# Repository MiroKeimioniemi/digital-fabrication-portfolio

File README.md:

# Digital Fabrication Portfolio

[My Digital Fabrication Portfolio](https://digital-fabrication-portfolio-miro-keimioniemi-a2f2c11a6e705b8f.gitlab.io/) created for the 2024 [Digital Fabrication](https://www.aalto.fi/en/minors/digital-fabrication-minor) [Fab Academy](https://fabacademy.org/) overlay course at [Aalto Fablab](https://studios.aalto.fi/fablab/), containing extensive documentation for 6 months worth of hands-on learning in the domains of:
- [project management](https://digital-fabrication-portfolio-miro-keimioniemi-a2f2c11a6e705b8f.gitlab.io/p/project-management/)
- [web development](https://digital-fabrication-portfolio-miro-keimioniemi-a2f2c11a6e705b8f.gitlab.io/p/project-management/)
- [parametric 3D design and rendering](https://digital-fabrication-portfolio-miro-keimioniemi-a2f2c11a6e705b8f.gitlab.io/p/computer-aided-design/)
- [laser and vinyl cutting](https://digital-fabrication-portfolio-miro-keimioniemi-a2f2c11a6e705b8f.gitlab.io/p/computer-controlled-cutting/)
- [heat pressing](https://digital-fabrication-portfolio-miro-keimioniemi-a2f2c11a6e705b8f.gitlab.io/p/computer-controlled-cutting/)
- [CNC milling](https://digital-fabrication-portfolio-miro-keimioniemi-a2f2c11a6e705b8f.gitlab.io/p/computer-controlled-machining/)
- [electronics production](https://digital-fabrication-portfolio-miro-keimioniemi-a2f2c11a6e705b8f.gitlab.io/p/electronics-production/)
- [3D printing and scanning](https://digital-fabrication-portfolio-miro-keimioniemi-a2f2c11a6e705b8f.gitlab.io/p/3d-printing-scanning/)
- [embedded programming](https://digital-fabrication-portfolio-miro-keimioniemi-a2f2c11a6e705b8f.gitlab.io/p/embedded-programming/)
- [electronics design](https://digital-fabrication-portfolio-miro-keimioniemi-a2f2c11a6e705b8f.gitlab.io/p/electronics-design/)
- [input devices](https://digital-fabrication-portfolio-miro-keimioniemi-a2f2c11a6e705b8f.gitlab.io/p/input-devices/)
- [output devices](https://digital-fabrication-portfolio-miro-keimioniemi-a2f2c11a6e705b8f.gitlab.io/p/output-devices/)
- [molding and casting](https://digital-fabrication-portfolio-miro-keimioniemi-a2f2c11a6e705b8f.gitlab.io/p/molding-casting/)
- [networking and communications](https://digital-fabrication-portfolio-miro-keimioniemi-a2f2c11a6e705b8f.gitlab.io/p/networking-and-communications/)
- [interface and application programming](https://digital-fabrication-portfolio-miro-keimioniemi-a2f2c11a6e705b8f.gitlab.io/p/interface-and-application-programming/)
- [3-axis milling](https://digital-fabrication-portfolio-miro-keimioniemi-a2f2c11a6e705b8f.gitlab.io/p/3-axis-milling-vacuum-forming-wildcard/)
- [vacuum forming](https://digital-fabrication-portfolio-miro-keimioniemi-a2f2c11a6e705b8f.gitlab.io/p/3-axis-milling-vacuum-forming-wildcard/)
- [system integration](https://digital-fabrication-portfolio-miro-keimioniemi-a2f2c11a6e705b8f.gitlab.io/p/system-integration/) 

...creating varied unique projects such as: 
- [this website](https://digital-fabrication-portfolio-miro-keimioniemi-a2f2c11a6e705b8f.gitlab.io/p/project-management/)
- [3D renders](https://digital-fabrication-portfolio-miro-keimioniemi-a2f2c11a6e705b8f.gitlab.io/p/computer-aided-design/)
- [a parametric dragon construction kit](https://digital-fabrication-portfolio-miro-keimioniemi-a2f2c11a6e705b8f.gitlab.io/p/computer-controlled-cutting/)
- [prints on a hoodie](https://digital-fabrication-portfolio-miro-keimioniemi-a2f2c11a6e705b8f.gitlab.io/p/computer-controlled-cutting/)
- [printed circuit boards (PCB)](https://digital-fabrication-portfolio-miro-keimioniemi-a2f2c11a6e705b8f.gitlab.io/p/electronics-design/)
- [keychains](https://digital-fabrication-portfolio-miro-keimioniemi-a2f2c11a6e705b8f.gitlab.io/p/3d-printing-scanning/)
- [3D models of real objects](https://digital-fabrication-portfolio-miro-keimioniemi-a2f2c11a6e705b8f.gitlab.io/p/3d-printing-scanning/)
- [embedded games](https://digital-fabrication-portfolio-miro-keimioniemi-a2f2c11a6e705b8f.gitlab.io/p/embedded-programming/)
- [design shelves](https://digital-fabrication-portfolio-miro-keimioniemi-a2f2c11a6e705b8f.gitlab.io/p/computer-controlled-machining/)
- [lightsabers](https://digital-fabrication-portfolio-miro-keimioniemi-a2f2c11a6e705b8f.gitlab.io/p/molding-casting/)
- [a mobile app](https://digital-fabrication-portfolio-miro-keimioniemi-a2f2c11a6e705b8f.gitlab.io/p/interface-and-application-programming/) 

...and most notably; [a gesture controlled lamp](https://digital-fabrication-portfolio-miro-keimioniemi-a2f2c11a6e705b8f.gitlab.io/final-project/) integrating most of the processes learned into one larger prototype as the course final project.

The website is deployed at [https://digital-fabrication-portfolio-miro-keimioniemi-a2f2c11a6e705b8f.gitlab.io/](https://digital-fabrication-portfolio-miro-keimioniemi-a2f2c11a6e705b8f.gitlab.io/), which can also be found at [mirokeimioniemi.com](https://mirokeimioniemi.com/).

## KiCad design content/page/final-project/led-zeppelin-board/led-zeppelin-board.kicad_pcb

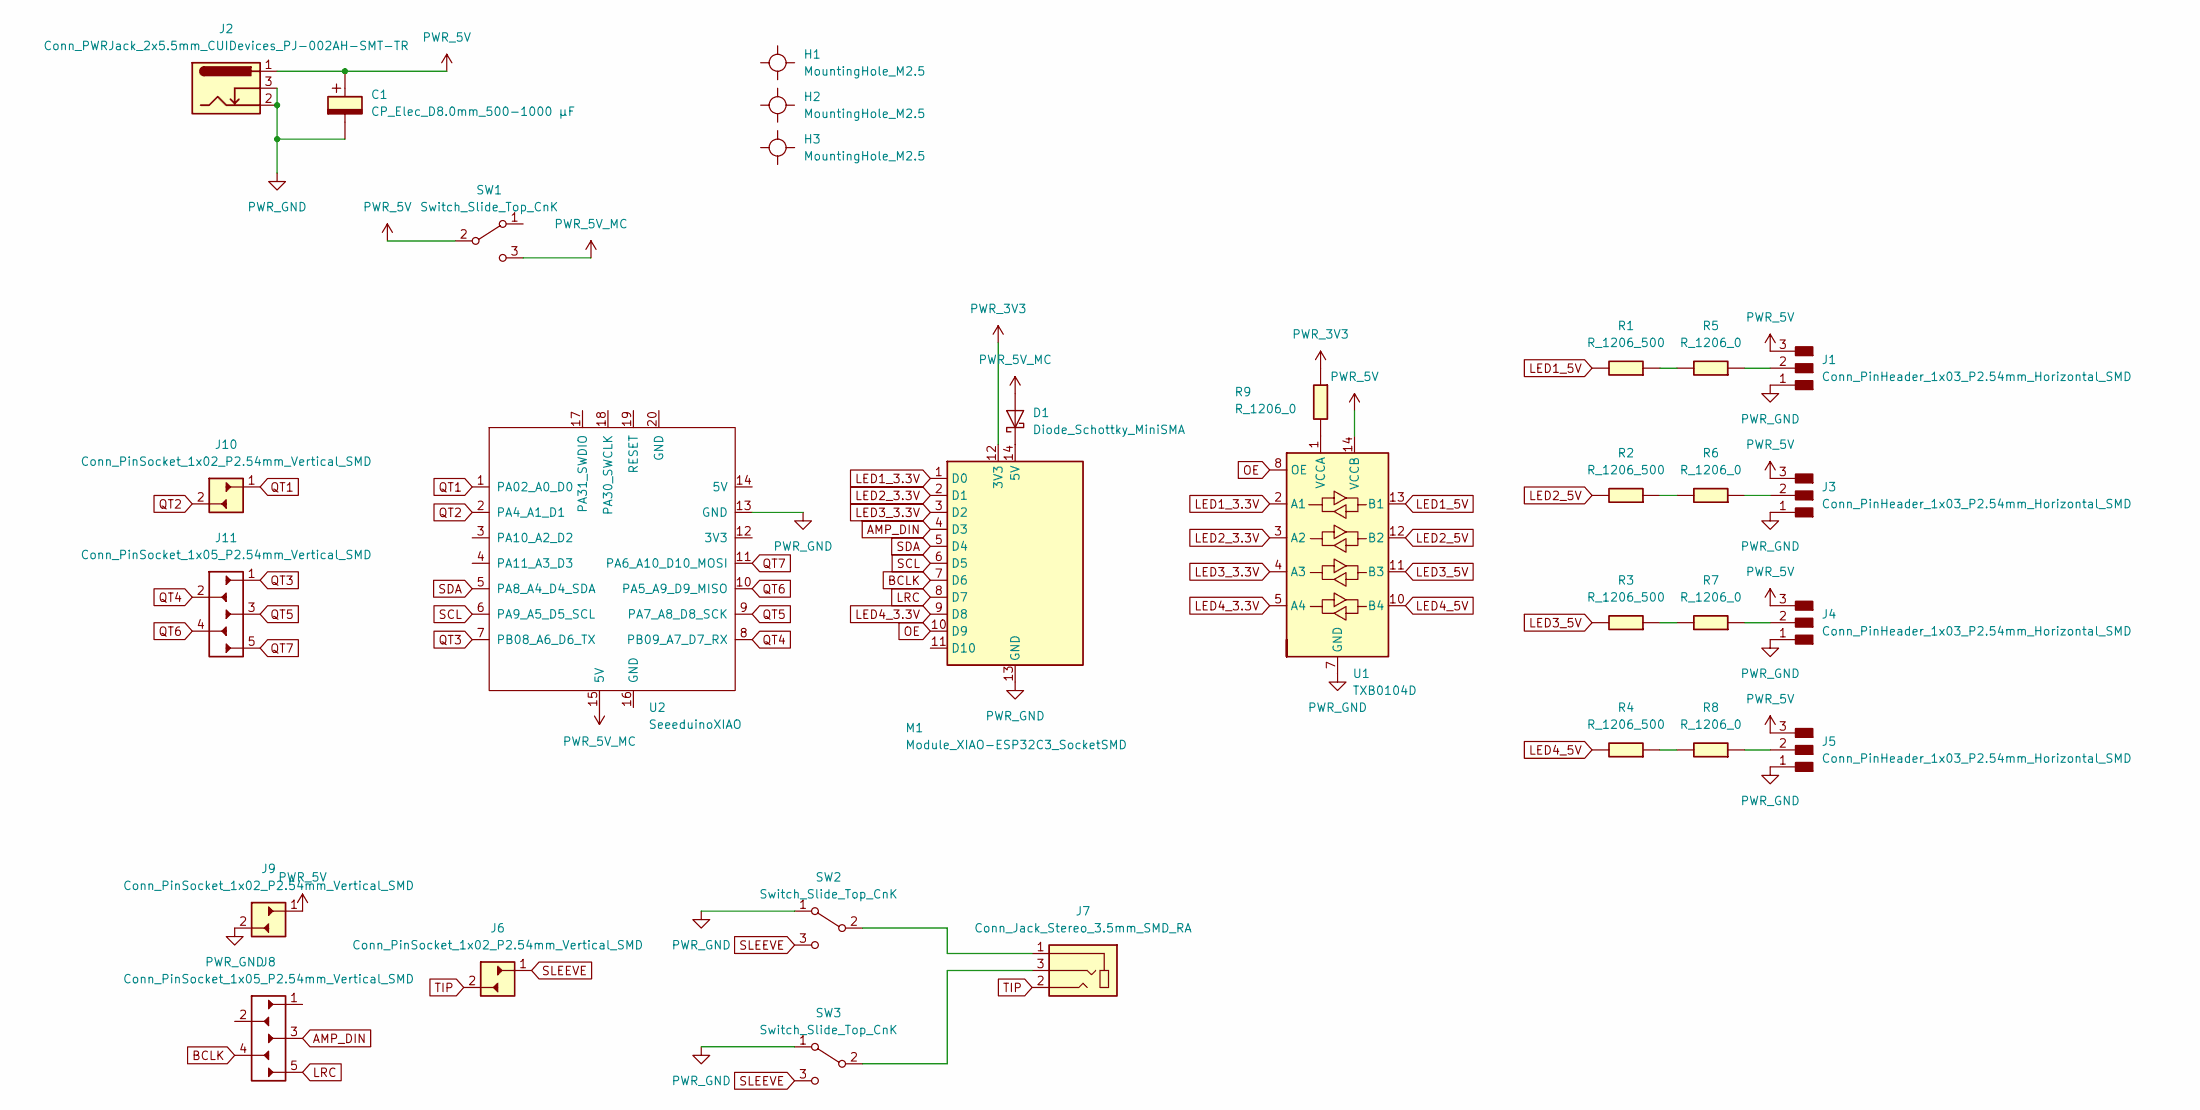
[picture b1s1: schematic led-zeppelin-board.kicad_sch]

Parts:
C1: CP_Elec_D8.0mm_500-1000 µF; CP_Elec_D8.0mm
D1: Diode_Schottky_MiniSMA; SOD-123T
H1, H2, H3: MountingHole_M2.5
J1, J3, J4, J5: Conn_PinHeader_1x03_P2.54mm_Horizontal_SMD; PinHeader_1x03_P2.54mm_Horizontal_SMD
J2: Conn_PWRJack_2x5.5mm_CUIDevices_PJ-002AH-SMT-TR; CUIDevices_PJ-002AH-SMT-TR_PWRJack_2x5.5mm
J6, J9, J10: Conn_PinSocket_1x02_P2.54mm_Vertical_SMD; PinSocket_1x02_P2.54mm_Vertical_SMD
J7: Conn_Jack_Stereo_3.5mm_SMD_RA; Conn_Jack_Stereo_3.5mm_CUI_SJ-3523-SMT-TR
J8, J11: Conn_PinSocket_1x05_P2.54mm_Vertical_SMD; PinSocket_1x05_P2.54mm_Vertical_SMD
M1: Module_XIAO-ESP32C3_SocketSMD; SeeedStudio_XIAO_SocketSMD
R1, R2, R3, R4: R_1206_500; R_1206
R5, R6, R7, R8, R9: R_1206_0; R_1206
SW1, SW2, SW3: Switch_Slide_Top_CnK; Switch_Slide_Top_CnK_JS102011JCQN_8.5x3.5mm
U1: TXB0104D; SOIC-14_3.9x8.7mm_P1.27mm
U2: SeeeduinoXIAO; SeeedStudio_XIAO_SocketSMD

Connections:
AMP_DIN: J8.3 (Pin_1), M1.4 (D3)
BCLK: J8.4 (Pin_2), M1.7 (D6)
LED1_3.3V: M1.1 (D0), U1.2 (A1)
LED1_5V: R1.1, U1.13 (B1)
LED2_3.3V: M1.2 (D1), U1.3 (A2)
LED2_5V: R2.1, U1.12 (B2)
LED3_3.3V: M1.3 (D2), U1.4 (A3)
LED3_5V: R3.1, U1.11 (B3)
LED4_3.3V: M1.9 (D8), U1.5 (A4)
LED4_5V: R4.1, U1.10 (B4)
LRC: J8.5 (Pin_1), M1.8 (D7)
unnamed: D1.1 (K), M1.14 (5V)
unnamed: J1.2, R5.2
unnamed: J3.2, R6.2
unnamed: J4.2, R7.2
unnamed: J5.2, R8.2
unnamed: R1.2, R5.1
unnamed: R2.2, R6.1
unnamed: R3.2, R7.1
unnamed: R4.2, R8.1
unnamed: J7.1, SW2.2 (B)
unnamed: J7.3, SW3.2 (B)
unnamed: R9.1, U1.1 (VCCA)
OE: M1.10 (D9), U1.8 (OE)
PWR_3V3: M1.12 (3V3), R9.2
PWR_5V: C1.1, J1.3, J2.1, J3.3, J4.3, J5.3, J9.1, SW1.2 (B), U1.14 (VCCB)
PWR_5V_MC: D1.2 (A), SW1.3 (C), U2.15 (5V)
PWR_GND: C1.2, J1.1, J2.2, J2.3, J3.1, J4.1, J5.1, J9.2, M1.13 (GND), SW2.1 (A), SW3.1 (A), U1.7 (GND), U2.13 (GND)
QT1: J10.1, U2.1 (PA02_A0_D0)
QT2: J10.2, U2.2 (PA4_A1_D1)
QT3: J11.1, U2.7 (PB08_A6_D6_TX)
QT4: J11.2, U2.8 (PB09_A7_D7_RX)
QT5: J11.3 (Pin_1), U2.9 (PA7_A8_D8_SCK)
QT6: J11.4 (Pin_2), U2.10 (PA5_A9_D9_MISO)
QT7: J11.5 (Pin_1), U2.11 (PA6_A10_D10_MOSI)
SCL: M1.6 (D5), U2.6 (PA9_A5_D5_SCL)
SDA: M1.5 (D4), U2.5 (PA8_A4_D4_SDA)
SLEEVE: J6.1, SW2.3 (C), SW3.3 (C)
TIP: J6.2, J7.2

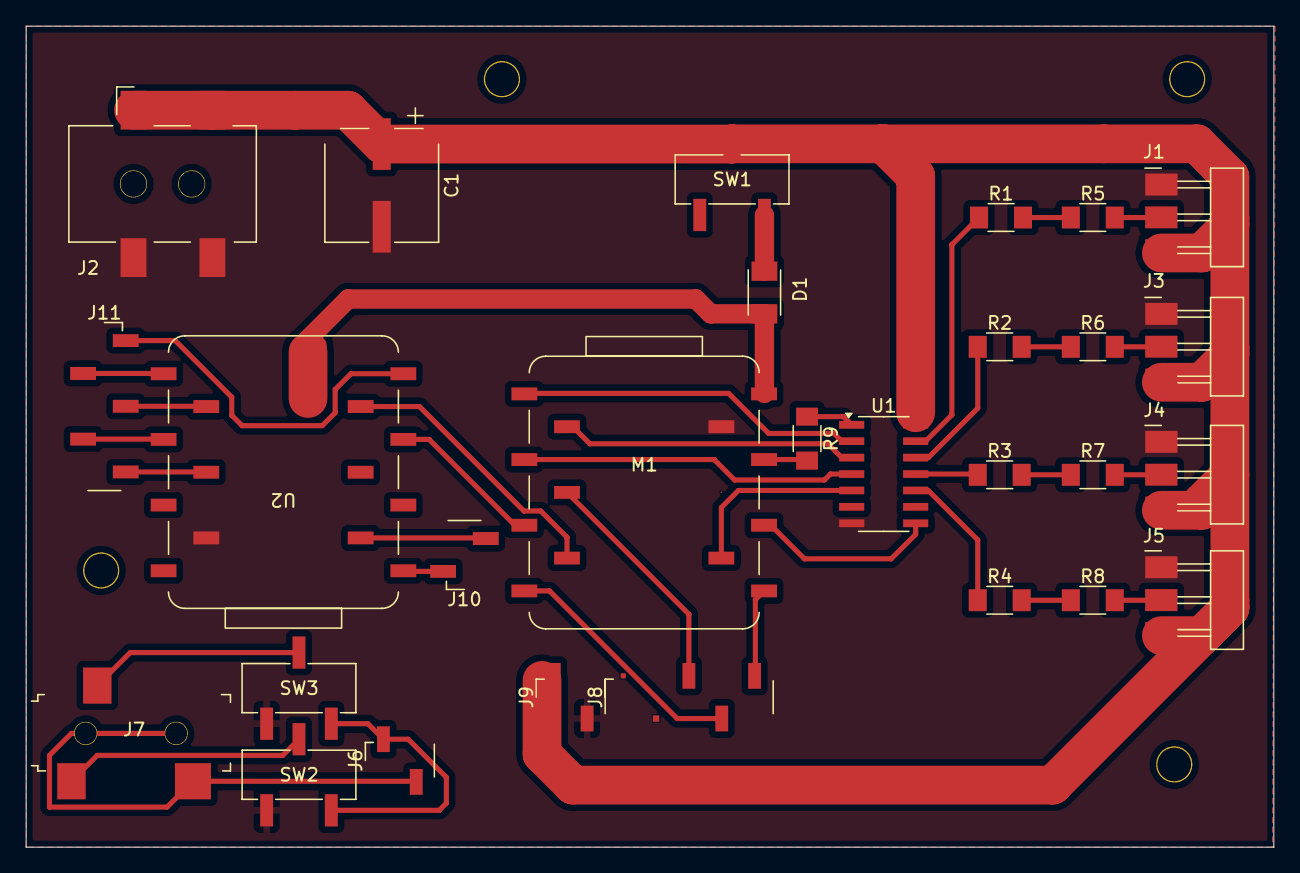
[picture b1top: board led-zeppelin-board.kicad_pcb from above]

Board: 2 copper layers, 96.5 x 63.5 mm, 32 parts (0 on the bottom side), 39 nets.

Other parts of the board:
H2#2: MountingHole_M2.5

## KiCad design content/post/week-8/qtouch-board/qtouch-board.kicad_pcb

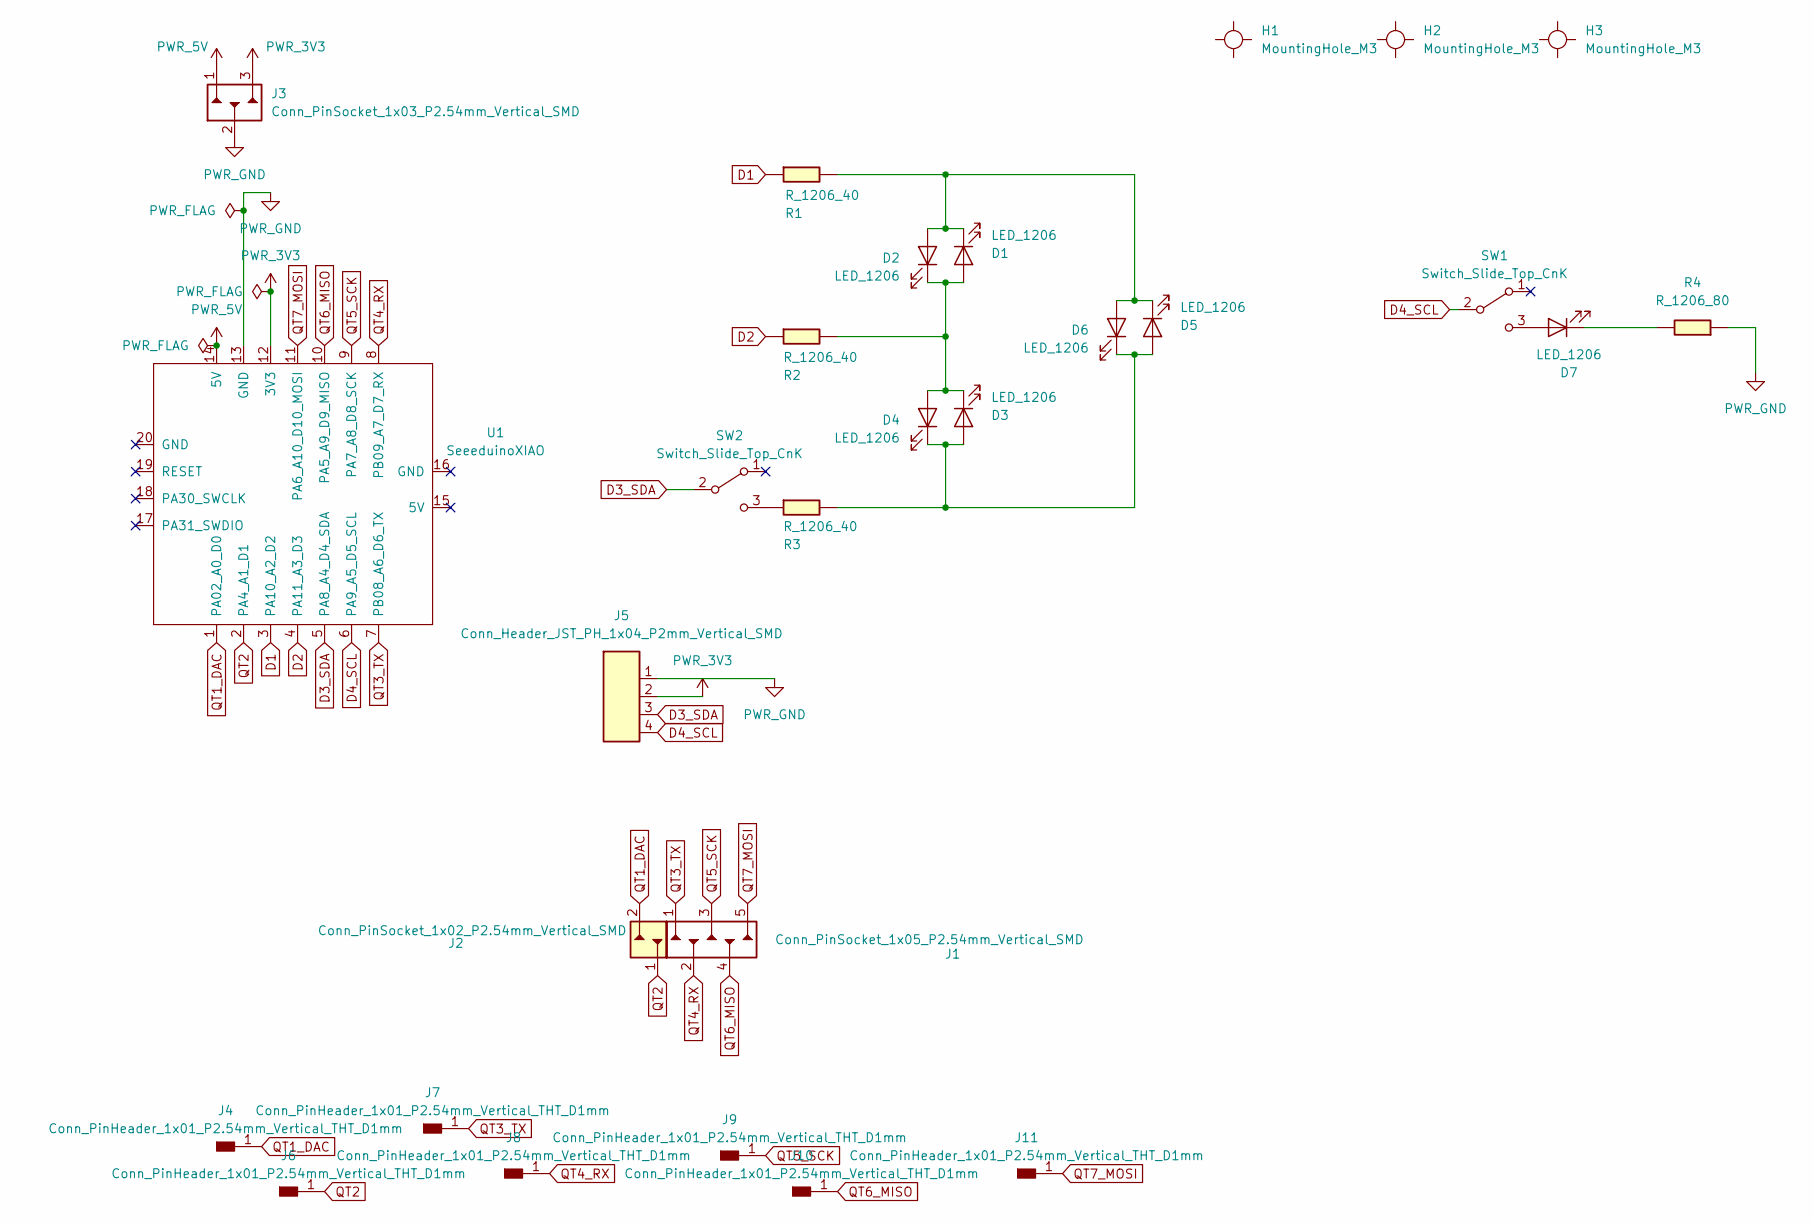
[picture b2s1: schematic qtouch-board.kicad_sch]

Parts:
D1, D2, D3, D4, D5, D6, D7: LED_1206
H1, H2, H3: MountingHole_M3
J1: Conn_PinSocket_1x05_P2.54mm_Vertical_SMD; PinSocket_1x05_P2.54mm_Vertical_SMD
J2: Conn_PinSocket_1x02_P2.54mm_Vertical_SMD; PinSocket_1x02_P2.54mm_Vertical_SMD
J3: Conn_PinSocket_1x03_P2.54mm_Vertical_SMD; PinSocket_1x03_P2.54mm_Vertical_SMD
J4, J6, J7, J8, J9, J10, J11: Conn_PinHeader_1x01_P2.54mm_Vertical_THT_D1mm; PinHeader_1x01_P2.54mm_Vertical_THT_D1mm
J5: Conn_Header_JST_PH_1x04_P2mm_Vertical_SMD; Header_JST_PH_1x04_P2mm_Vertical_SMD
R1, R2, R3: R_1206_40; R_1206
R4: R_1206_80; R_1206
SW1, SW2: Switch_Slide_Top_CnK; Switch_Slide_Top_CnK_JS102011JCQN_8.5x3.5mm
U1: SeeeduinoXIAO; SeeedStudio_XIAO_SocketSMD

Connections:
D1: R1.2, U1.3 (PA10_A2_D2)
D2: R2.2, U1.4 (PA11_A3_D3)
D3_SDA: J5.3, SW2.2 (B), U1.5 (PA8_A4_D4_SDA)
D4_SCL: J5.4, SW1.2 (B), U1.6 (PA9_A5_D5_SCL)
unnamed: D1.2 (A), D2.1 (K), D3.1 (K), D4.2 (A), R2.1
unnamed: D1.1 (K), D2.2 (A), D5.1 (K), D6.2 (A), R1.1
unnamed: D3.2 (A), D4.1 (K), D5.2 (A), D6.1 (K), R3.1
unnamed: D7.2 (A), SW1.3 (C)
unnamed: D7.1 (K), R4.1
unnamed: R3.2, SW2.3 (C)
PWR_3V3: J3.3 (Pin_1), J5.2, U1.12 (3V3)
PWR_5V: J3.1, U1.14 (5V)
PWR_GND: J3.2, J5.1, R4.2, U1.13 (GND)
QT1_DAC: J2.2, J4.1, U1.1 (PA02_A0_D0)
QT2: J2.1, J6.1, U1.2 (PA4_A1_D1)
QT3_TX: J1.1, J7.1, U1.7 (PB08_A6_D6_TX)
QT4_RX: J1.2, J8.1, U1.8 (PB09_A7_D7_RX)
QT5_SCK: J1.3 (Pin_1), J9.1, U1.9 (PA7_A8_D8_SCK)
QT6_MISO: J1.4 (Pin_2), J10.1, U1.10 (PA5_A9_D9_MISO)
QT7_MOSI: J1.5 (Pin_1), J11.1, U1.11 (PA6_A10_D10_MOSI)

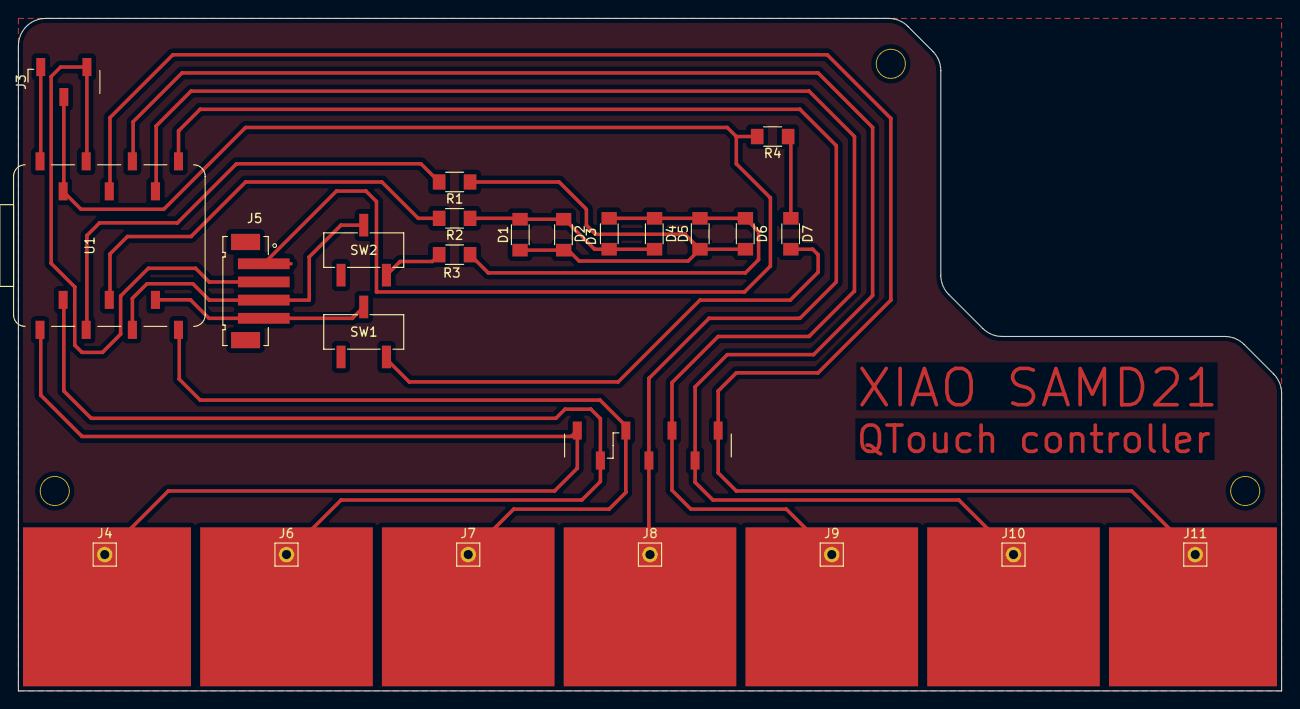
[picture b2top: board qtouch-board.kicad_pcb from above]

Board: 2 copper layers, 139.0 x 74.0 mm, 28 parts (0 on the bottom side), 20 nets.

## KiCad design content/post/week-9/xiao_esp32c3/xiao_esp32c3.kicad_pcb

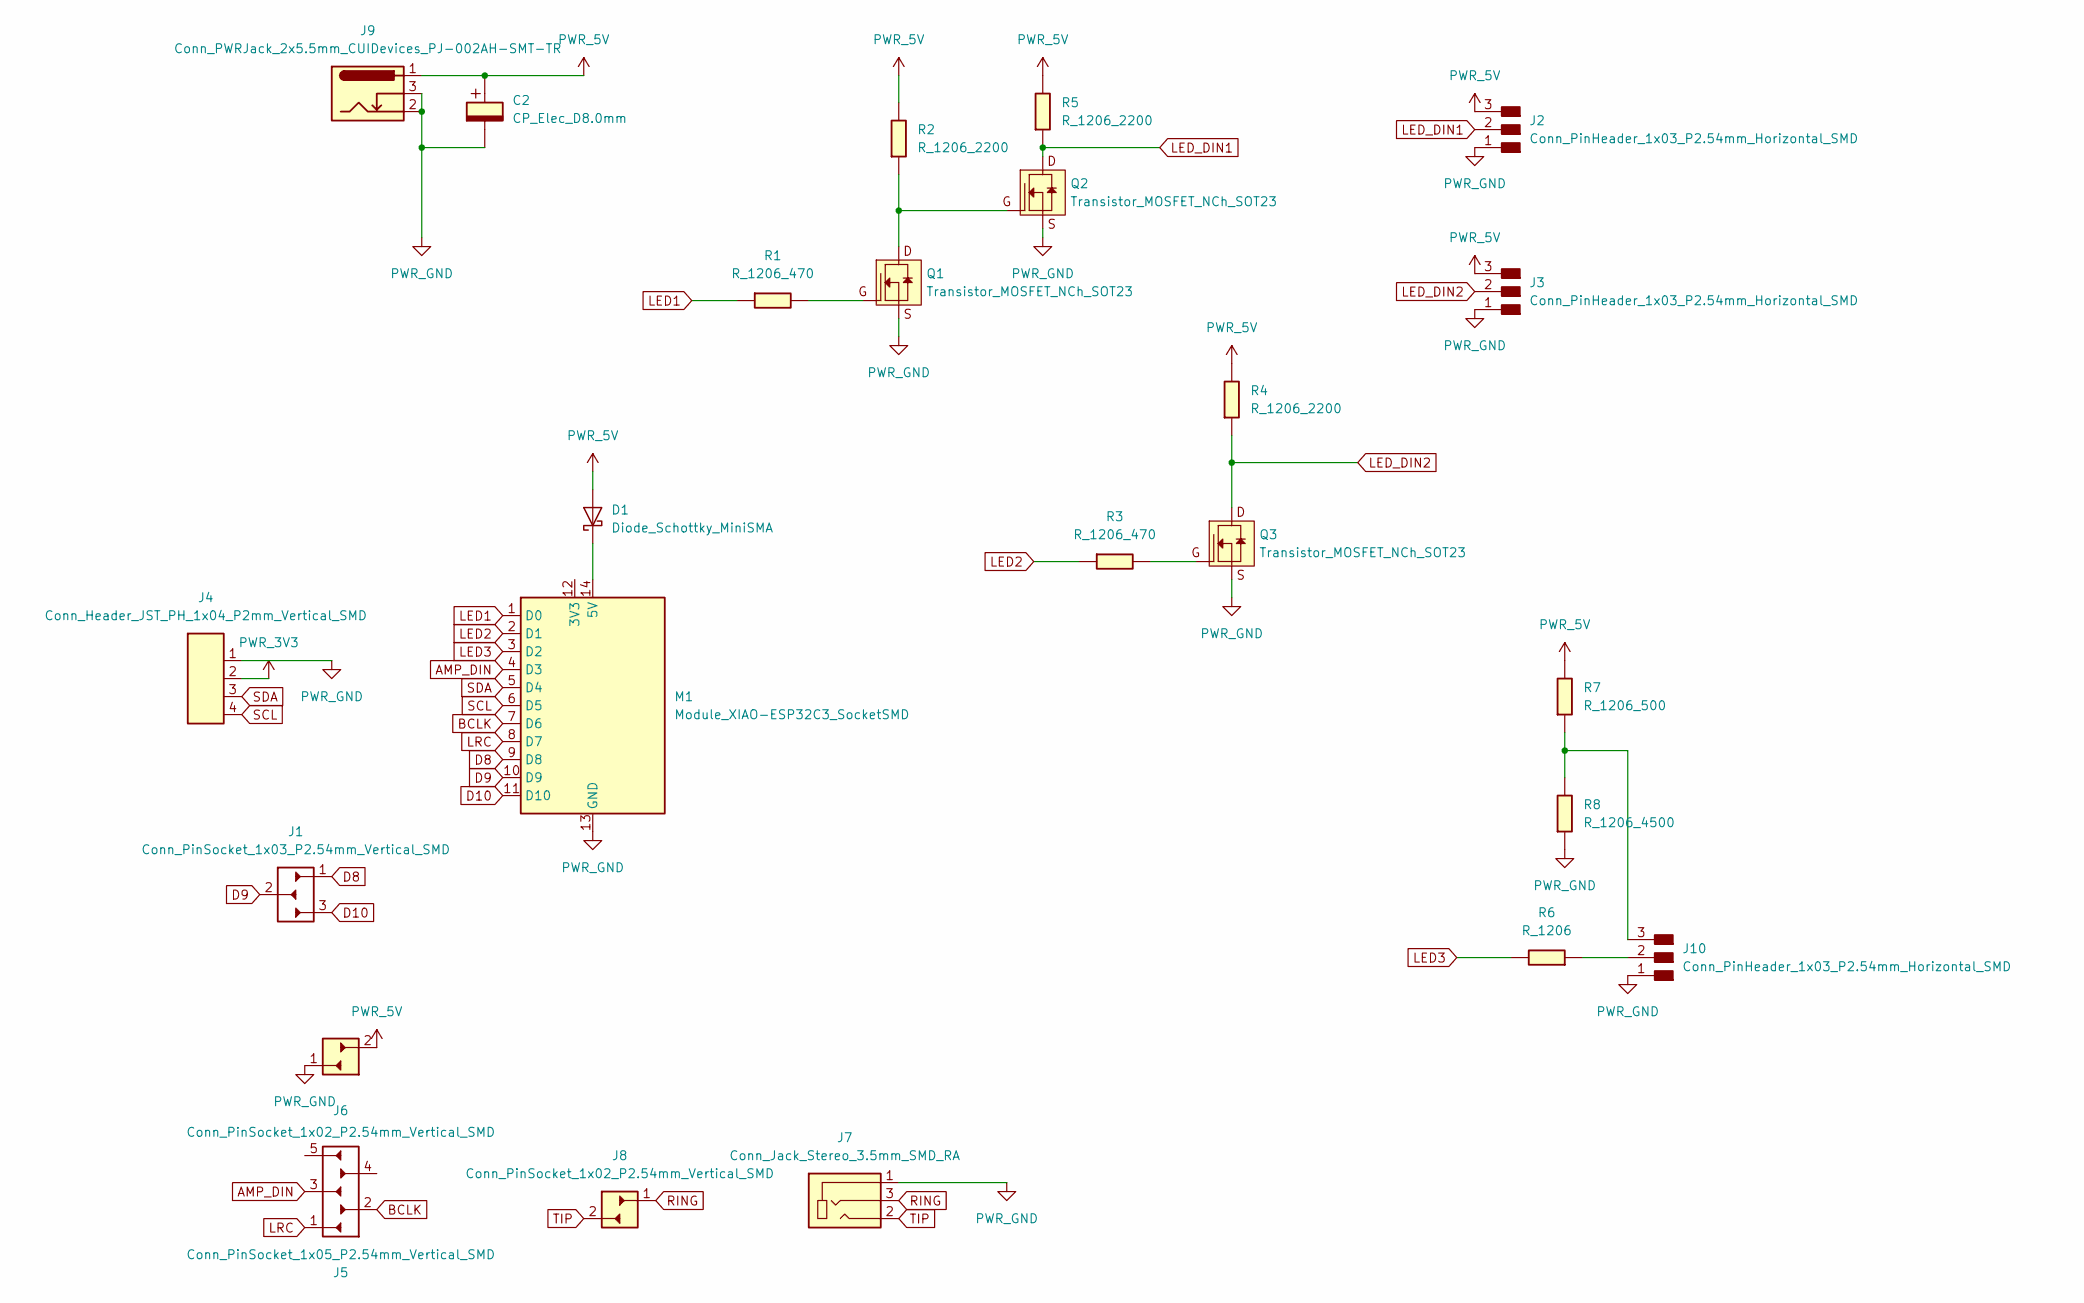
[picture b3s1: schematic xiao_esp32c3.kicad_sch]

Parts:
C2: CP_Elec_D8.0mm
D1: Diode_Schottky_MiniSMA; SOD-123T
J1: Conn_PinSocket_1x03_P2.54mm_Vertical_SMD; PinSocket_1x03_P2.54mm_Vertical_SMD
J2, J3, J10: Conn_PinHeader_1x03_P2.54mm_Horizontal_SMD; PinHeader_1x03_P2.54mm_Horizontal_SMD
J4: Conn_Header_JST_PH_1x04_P2mm_Vertical_SMD; Header_JST_PH_1x04_P2mm_Vertical_SMD
J5: Conn_PinSocket_1x05_P2.54mm_Vertical_SMD; PinSocket_1x05_P2.54mm_Vertical_SMD
J6, J8: Conn_PinSocket_1x02_P2.54mm_Vertical_SMD; PinSocket_1x02_P2.54mm_Vertical_SMD
J7: Conn_Jack_Stereo_3.5mm_SMD_RA; Conn_Jack_Stereo_3.5mm_CUI_SJ-3523-SMT-TR
J9: Conn_PWRJack_2x5.5mm_CUIDevices_PJ-002AH-SMT-TR; CUIDevices_PJ-002AH-SMT-TR_PWRJack_2x5.5mm
M1: Module_XIAO-ESP32C3_SocketSMD; SeeedStudio_XIAO_SocketSMD
Q1, Q2, Q3: Transistor_MOSFET_NCh_SOT23; SOT-23-3
R1, R3: R_1206_470; R_1206
R2, R4, R5: R_1206_2200; R_1206
R6: R_1206
R7: R_1206_500; R_1206
R8: R_1206_4500; R_1206

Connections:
AMP_DIN: J5.3 (Pin_1), M1.4 (D3)
BCLK: J5.2, M1.7 (D6)
D8: J1.1, M1.9 (D8)
D9: J1.2, M1.10 (D9)
D10: J1.3 (Pin_1), M1.11 (D10)
LED1: M1.1 (D0), R1.2
LED2: M1.2 (D1), R3.2
LED3: M1.3 (D2), R6.1
LED_DIN1: J2.2, Q2.3 (D), R5.2
LED_DIN2: J3.2, Q3.3 (D), R4.2
LRC: J5.1, M1.8 (D7)
unnamed: D1.1 (K), M1.14 (5V)
unnamed: J10.2, R6.2
unnamed: J10.3, R7.2, R8.1
unnamed: Q1.3 (D), Q2.1 (G), R2.2
unnamed: Q1.1 (G), R1.1
unnamed: Q3.1 (G), R3.1
PWR_3V3: J4.2
PWR_5V: C2.1, D1.2 (A), J2.3, J3.3, J6.2, J9.1, R2.1, R4.1, R5.1, R7.1
PWR_GND: C2.2, J2.1, J3.1, J4.1, J6.1, J7.1, J9.2, J9.3, J10.1, M1.13 (GND), Q1.2 (S), Q2.2 (S), Q3.2 (S), R8.2
RING: J7.3, J8.1
SCL: J4.4, M1.6 (D5)
SDA: J4.3, M1.5 (D4)
TIP: J7.2, J8.2

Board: 2 copper layers, 24 parts (0 on the bottom side), 23 nets, no tracks yet.

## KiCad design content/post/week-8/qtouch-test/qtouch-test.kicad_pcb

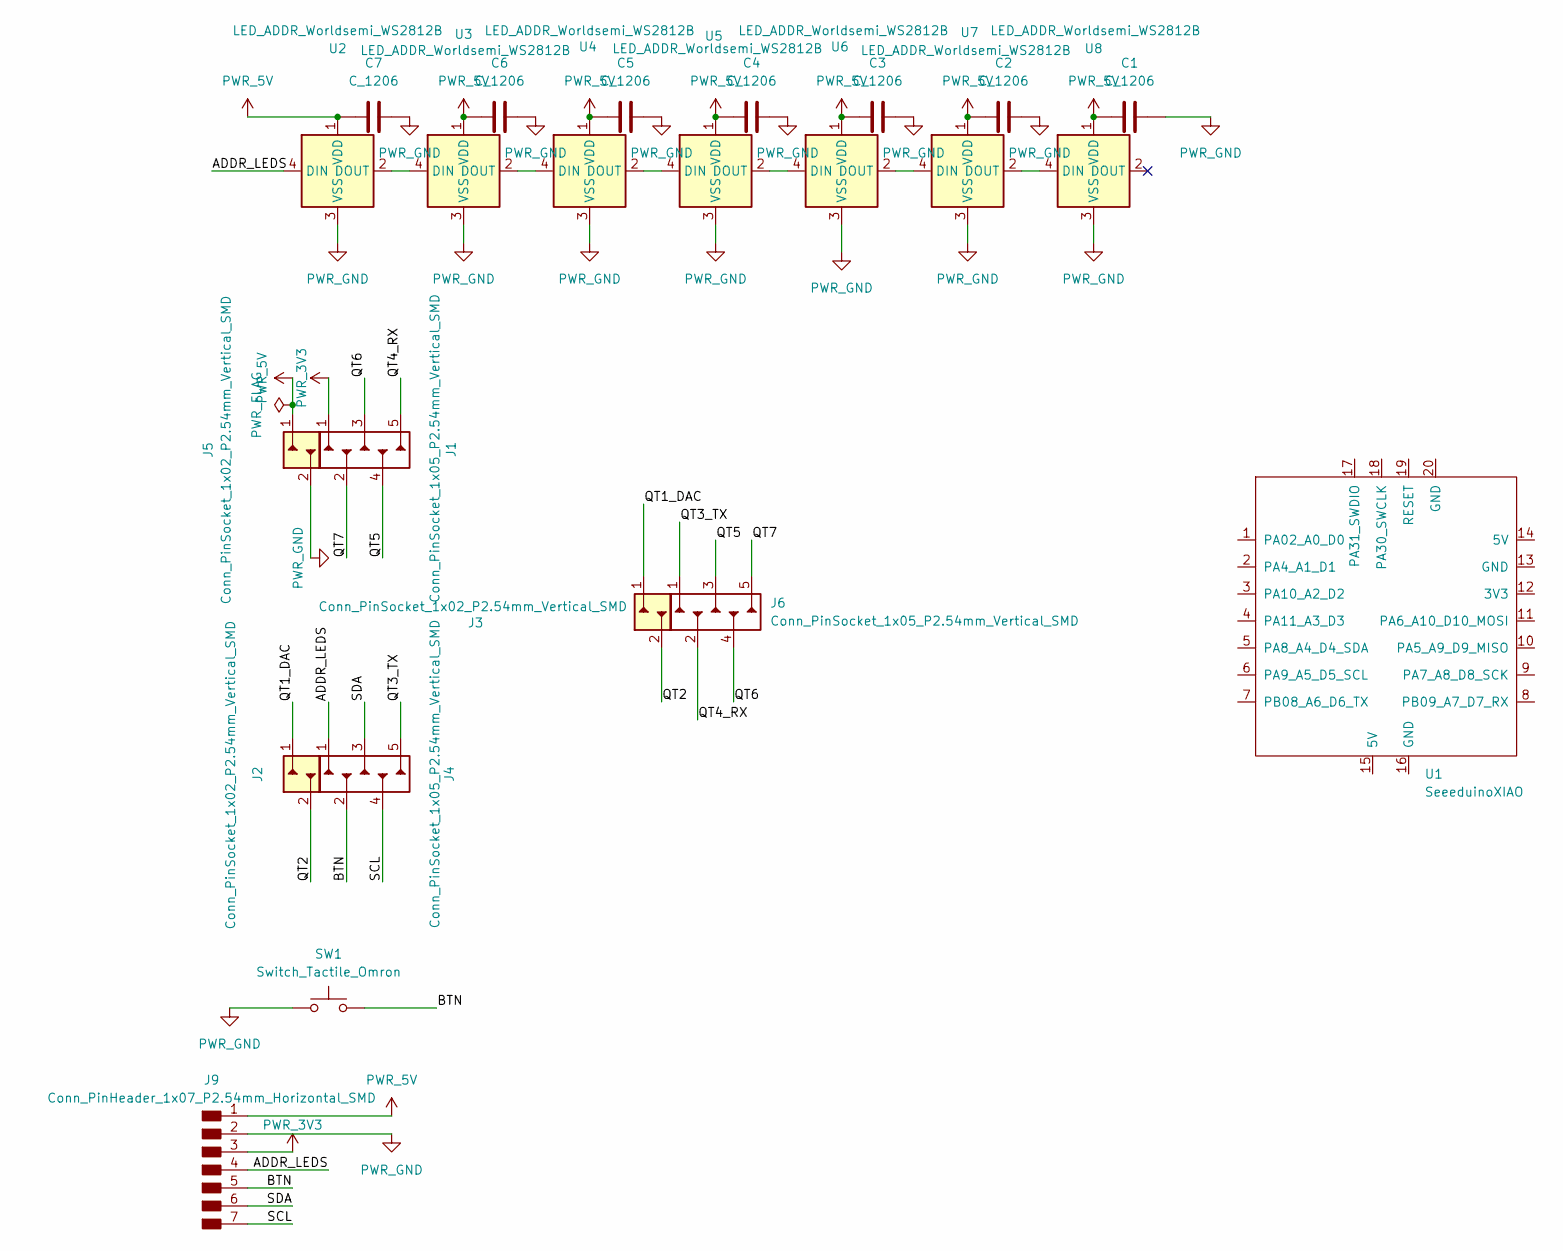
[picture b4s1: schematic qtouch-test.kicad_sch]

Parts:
C1, C2, C3, C4, C5, C6, C7: C_1206
J1, J4, J6: Conn_PinSocket_1x05_P2.54mm_Vertical_SMD; PinSocket_1x05_P2.54mm_Vertical_SMD
J2, J3, J5: Conn_PinSocket_1x02_P2.54mm_Vertical_SMD; PinSocket_1x02_P2.54mm_Vertical_SMD
J9: Conn_PinHeader_1x07_P2.54mm_Horizontal_SMD; PinHeader_1x07_P2.54mm_Horizontal_SMD
SW1: Switch_Tactile_Omron; Button_Omron_B3SN_6.0x6.0mm
U1: SeeeduinoXIAO; SeeedStudio_XIAO_SocketSMD
U2, U3, U4, U5, U6, U7, U8: LED_ADDR_Worldsemi_WS2812B

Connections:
/ADDR_LEDS: J4.1, J9.4, U2.4 (DIN)
/BTN: J4.2, J9.5, SW1.2
/QT1_DAC: J2.1, J3.1
/QT2: J2.2, J3.2
/QT3_TX: J4.5 (Pin_1), J6.1
/QT4_RX: J1.5 (Pin_1), J6.2
/QT5: J1.4 (Pin_2), J6.3 (Pin_1)
/QT6: J1.3 (Pin_1), J6.4 (Pin_2)
/QT7: J1.2, J6.5 (Pin_1)
/SCL: J4.4 (Pin_2), J9.7
/SDA: J4.3 (Pin_1), J9.6
unnamed: U2.2 (DOUT), U3.4 (DIN)
unnamed: U3.2 (DOUT), U4.4 (DIN)
unnamed: U4.2 (DOUT), U5.4 (DIN)
unnamed: U5.2 (DOUT), U6.4 (DIN)
unnamed: U6.2 (DOUT), U7.4 (DIN)
unnamed: U7.2 (DOUT), U8.4 (DIN)
PWR_3V3: J1.1, J9.3
PWR_5V: C1.2, C2.2, C3.2, C4.2, C5.2, C6.2, C7.2, J5.1, J9.1, U2.1 (VDD), U3.1 (VDD), U4.1 (VDD), U5.1 (VDD), U6.1 (VDD), U7.1 (VDD), U8.1 (VDD)
PWR_GND: C1.1, C2.1, C3.1, C4.1, C5.1, C6.1, C7.1, J5.2, J9.2, SW1.1, U2.3 (VSS), U3.3 (VSS), U4.3 (VSS), U5.3 (VSS), U6.3 (VSS), U7.3 (VSS), U8.3 (VSS)

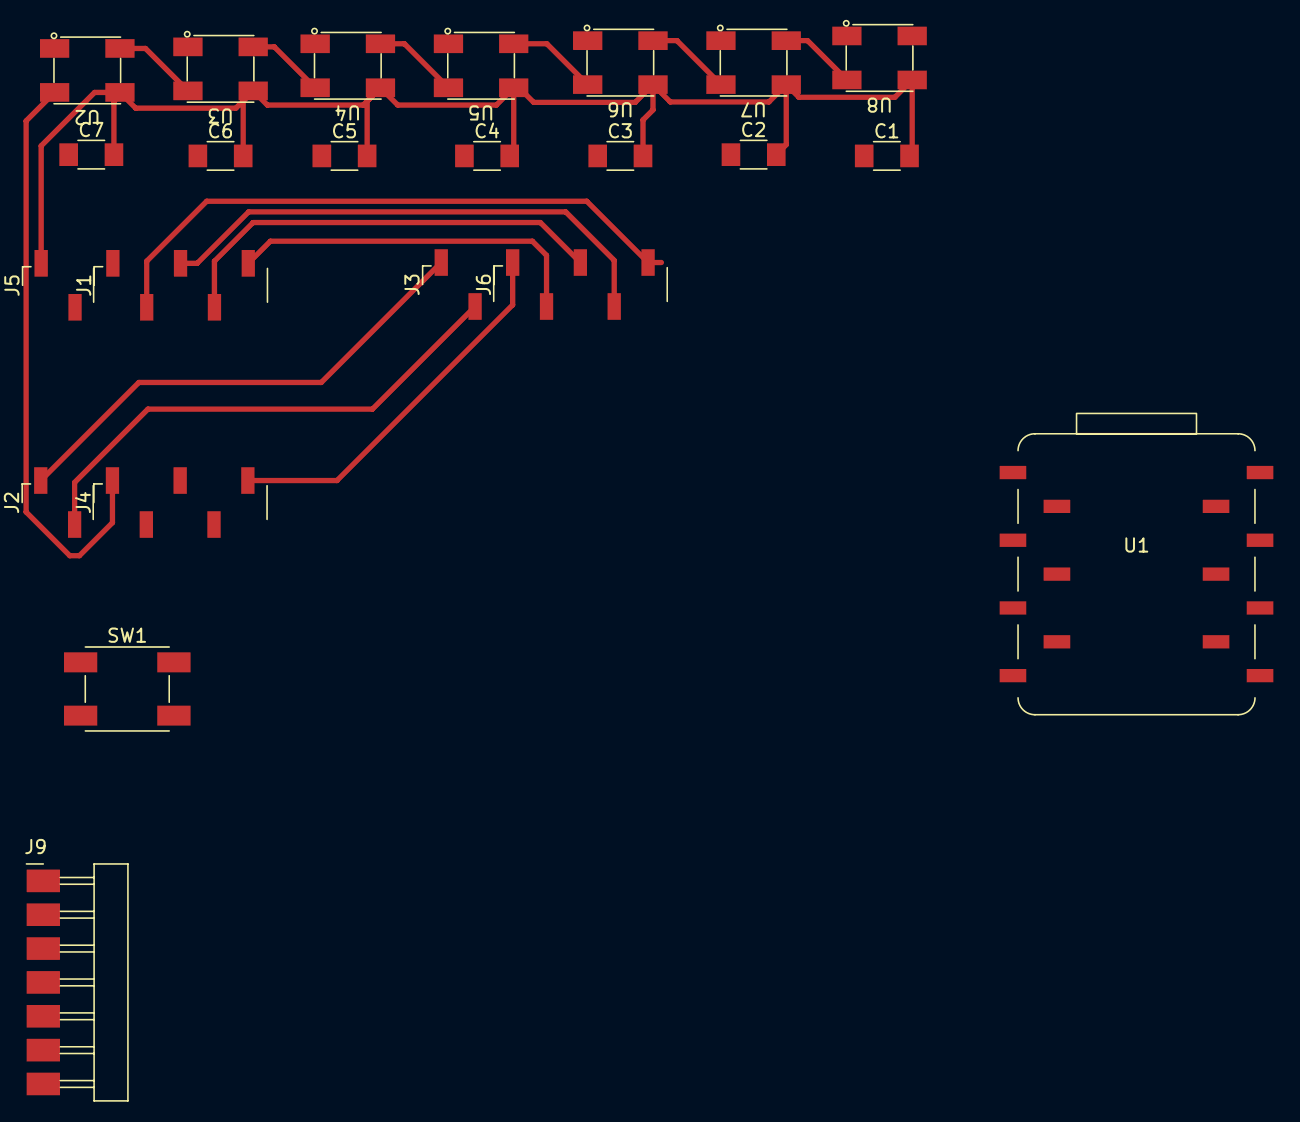
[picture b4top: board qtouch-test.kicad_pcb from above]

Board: 2 copper layers, 23 parts (0 on the bottom side), 20 nets.

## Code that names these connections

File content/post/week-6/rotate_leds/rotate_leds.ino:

#define LED1 D0
#define LED2 D6
#define LED3 D7
#define BTN D1

bool led1State = HIGH; // HIGH, true and 1 mean the same
bool led2State = HIGH;
bool led3State = HIGH;

int targetLED = 0;

bool btnState = HIGH; // button is high as it is connected to 3.3V via a pull-up resistor

void setup() {
  pinMode(LED1, OUTPUT);
  pinMode(LED2, OUTPUT);
  pinMode(LED3, OUTPUT);
  pinMode(BTN, INPUT);

  // set initial state of LEDs
  digitalWrite(LED1, led1State);
  digitalWrite(LED3, led2State);
  digitalWrite(LED2, led3State);
}

void loop() {
  bool btnReading = digitalRead(BTN);

  // we want to do something only if the reading and the state are different
  // in this case they are the same and we exit the loop immediatly
  if(btnReading == btnState){
    return; 
  }
 
  if(btnReading == LOW){ // LOW means button is pressed on Tarantino
    btnState = LOW;
    targetLED++;

    switch(targetLED % 3){
      case 0: 
        led1State = LOW;
        led2State = LOW;
        led3State = HIGH;
        break;
      case 1: 
        led1State = HIGH;
        led2State = LOW;
        led3State = LOW;
        break;
      case 2: 
        led1State = LOW;
        led2State = HIGH;
        led3State = LOW;
        break;
    }
  }else{
    btnState = HIGH;
  }

  digitalWrite(LED1, led1State);
  digitalWrite(LED2, led2State);
  digitalWrite(LED3, led3State);
  delay(10);
}

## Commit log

2024-01-13 Created a new hugo site and customized the Stack template
2024-01-13 Update .gitlab-ci.yml file
2024-01-13 Updated baseurl
2024-01-29 Adjusted scaling and margins
2024-01-29 Created the post-list widget to display weekly assignments in the sidebar, increased pagination to accomodate all upcoming posts on one page and removed excess icons
2024-01-29 Created the post-list widget to display weekly assignments in the sidebar, increased pagination to accomodate all upcoming posts on one page, added next and previous week buttons and removed excess i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
2024-01-29 Deleted most placeholder posts other than a couple that will be potentially useful references for the first weekly assignment post
2024-01-30 Created scripts to automatically resize and compress images in the content folder upon git push and started week 1 post
2024-01-30 Test picture
2024-01-30 Test image compression script
2024-01-30 Test update image names script
2024-01-30 Test updated update-image-names script
2024-01-30 Updated cover image
2024-01-30 Updated cover picture and turned off image processing
2024-01-30 Deleted the rest of the example pages and added a final project page
2024-01-30 Updated compress-images script
2024-01-30 modified compress-images script
2024-01-31 Wrote the documentation for the automated image compression pipeline
2024-01-31 Wrote about hugo and git
2024-02-01 Finished Hugo documentation and did some cleaning up
2024-02-01 Edited image styling to make them more card-like and adjusted compress-images script
2024-02-01 Finished "Setting up"
2024-02-01 Wrote preliminary final project ideas
2024-02-01 Updated final project images
2024-02-01 Finished the project management post
2024-02-01 Updated compress-images losssy cutoff to be 200kb and updated project management documentation accordingly
2024-02-01 Updated documentation of image size limits
2024-02-02 Added week 4 page and reversed pagination order
2024-02-03 Addded documentation on Gimp
2024-02-04 Wrote about past 3d modeling experience and Ondsel installation
2024-02-05 First steps with Ondsel documentation
2024-02-05 Replaced example image to see how higher resolution compression settings make it look
2024-02-05 Finished the 3D model of the lamp with the simplest stand
2024-02-07 Finished Ondsel documentation
2024-02-08 Blender documentation
2024-02-08 Documented Inkscape and fixed and reorganized some images
2024-02-08 Updated week 4 reflections
2024-02-08 Updated week-2 front matter
2024-02-10 Documentation for vinyl cutting preparation
2024-02-15 Finished documentation on computer-controlled cutting
2024-02-15 Edited reflections
2024-02-15 Edited week-3 reflections
2024-02-15 Small additions and changes to posts and week 3 final files
2024-02-22 Added week-4 (6)
2024-02-22 Fixed week-4 main image
2024-02-22 Fixed another picture
2024-02-22 Minor updates
2024-02-28 Added a shortcode for displaying 3D models with model-viewer, uploaded files and started week-5 documentation
2024-02-29 Finished week-5 designs section
2024-02-29 Added images of 3D scanning and printing results
2024-02-29 deleted a couple pictures
2024-02-29 fixed images in week-5
2024-02-29 Added 3D printing pictures to week 5
2024-02-29 Fixed images in week 5
2024-02-29 Annotated and renamed images in week 5
2024-03-01 Finished week-5 documentation
2024-03-05 Started week-8 documentation
2024-03-05 Added first program to week 8
2024-03-06 Added PlatformIO setup to week-6
2024-03-07 Added reaction game code and videos to week 6
2024-03-08 Finished week-6 documentation
2024-03-08 Added a cover image for week-6 and added some tags
2024-03-08 Fixed week-6 cover image
2024-03-14 Add files to week 7
2024-03-14 Started documentation in week-7
2024-03-14 Added an image
2024-03-15 Finished design documentation for week-7
2024-03-15 Changed date in week-7
2024-03-17 Small additions, trying to sync to repository
2024-03-17 Added cnc milling part to week 7
2024-03-21 Very incomplete commit to week 8
2024-04-03 Catching up with documentation for weeks 7 and 8
2024-04-04 Fixed images
2024-04-04 Finished documentation until creating the schematic
2024-04-05 More electronics design documentation
2024-04-05 Finished design section of week 8 documentation
2024-04-07 Finished week 8 documentation apart from testing
2024-04-08 Started week 9 documentation
2024-04-09 Added to week 7 documentation
2024-04-10 LEDs part of week-9 documentation
2024-04-11 maybe finished week-9 documentation
2024-04-11 Updated final project
2024-04-11 Update final project
2024-04-22 Finally fully finished week 9 documentation
2024-04-22 Fixed cover image smh
2024-04-23 Finished week-9 documentation
2024-04-24 Finished week-8 documentation
2024-04-26 Started molding and casting documentation
2024-04-26 fixed week 11 thumbnail
2024-04-27 Wrote more about the design in week-11
2024-04-27 Updated molding and casting documentation
2024-04-27 Started input devices documentation
2024-04-28 Added gesture recognition to input code
2024-05-02 Updated input and molding and casting stuff
2024-05-05 Added heat pressing documentation to computer controlled cutting week
2024-05-05 Added vinyl removal documentation to computer controlled cutting week
2024-05-07 Final project plan
2024-05-08 Added figma mockup to interface and application programming
2024-05-08 Added networking attempt
2024-05-08 Finished input devices documentation
2024-05-08 Updated molding and casting
2024-05-09 Finished molding part of molding and casting documentation
2024-05-09 Finished molding and casting week documentation
2024-05-09 Fixed week-11 cover image
2024-05-15 Added final board design and working I2C code to repository
2024-05-15 Finished final board design documentation
2024-05-15 Finished final board documentation
2024-05-16 Added i2c demo video
2024-05-16 Added system integration sketch
2024-05-23 Added system integration week and updated documentation in multiple places
2024-05-23 Calculated power budget in system integration
2024-05-27 Added wifi API code for ESP32C3
2024-05-28 Started bluetooth programming
2024-05-28 Control LEDs via bluetooth done
2024-05-30 Added bluetooth demo video
2024-05-30 more
2024-05-31 Added vacuum forming images
2024-06-04 Connected all networking code along with other modifications
2024-06-04 Improved tapping experience
2024-06-04 Added a very primitive brightening animation
2024-06-06 Updated esp32c3-bluetooth code
2024-06-06 Successful bluetooth notifications!! (still janky)
2024-06-06 Janky esp32c3 bidirectional bluetooth connection
2024-06-06 Added presentation.png poster
2024-06-06 Upload New File
2024-06-06 Add video to repo
2024-06-09 Commented the internal code of the lamp thoroughly
2024-06-11 Updated networking and communication
2024-06-15 Documented XIAO ESP32C3 side of BLE
2024-06-15 Finished networking and communications documentation
2024-06-16 Added bluetooth permissions configuration to networks documentation, finished design part of interface and application programming and started with the application
2024-06-16 Finished Interface and Application Programming documentation
2024-06-18 Started wildcard documentation
2024-06-18 Finished 3D-milling documentation
2024-06-18 Finished vacuum forming intro
2024-06-19 Finished wildcard documentation
2024-06-19 Finished system integration documentation
2024-06-20 Added some hero shots and a BOM to final project documentation
2024-06-20 Added documentation to final project page
2024-06-20 Finished final project page
2024-06-20 Added a link to about
2024-06-20 Add a license
2024-06-20 Uploaded presentation.png
